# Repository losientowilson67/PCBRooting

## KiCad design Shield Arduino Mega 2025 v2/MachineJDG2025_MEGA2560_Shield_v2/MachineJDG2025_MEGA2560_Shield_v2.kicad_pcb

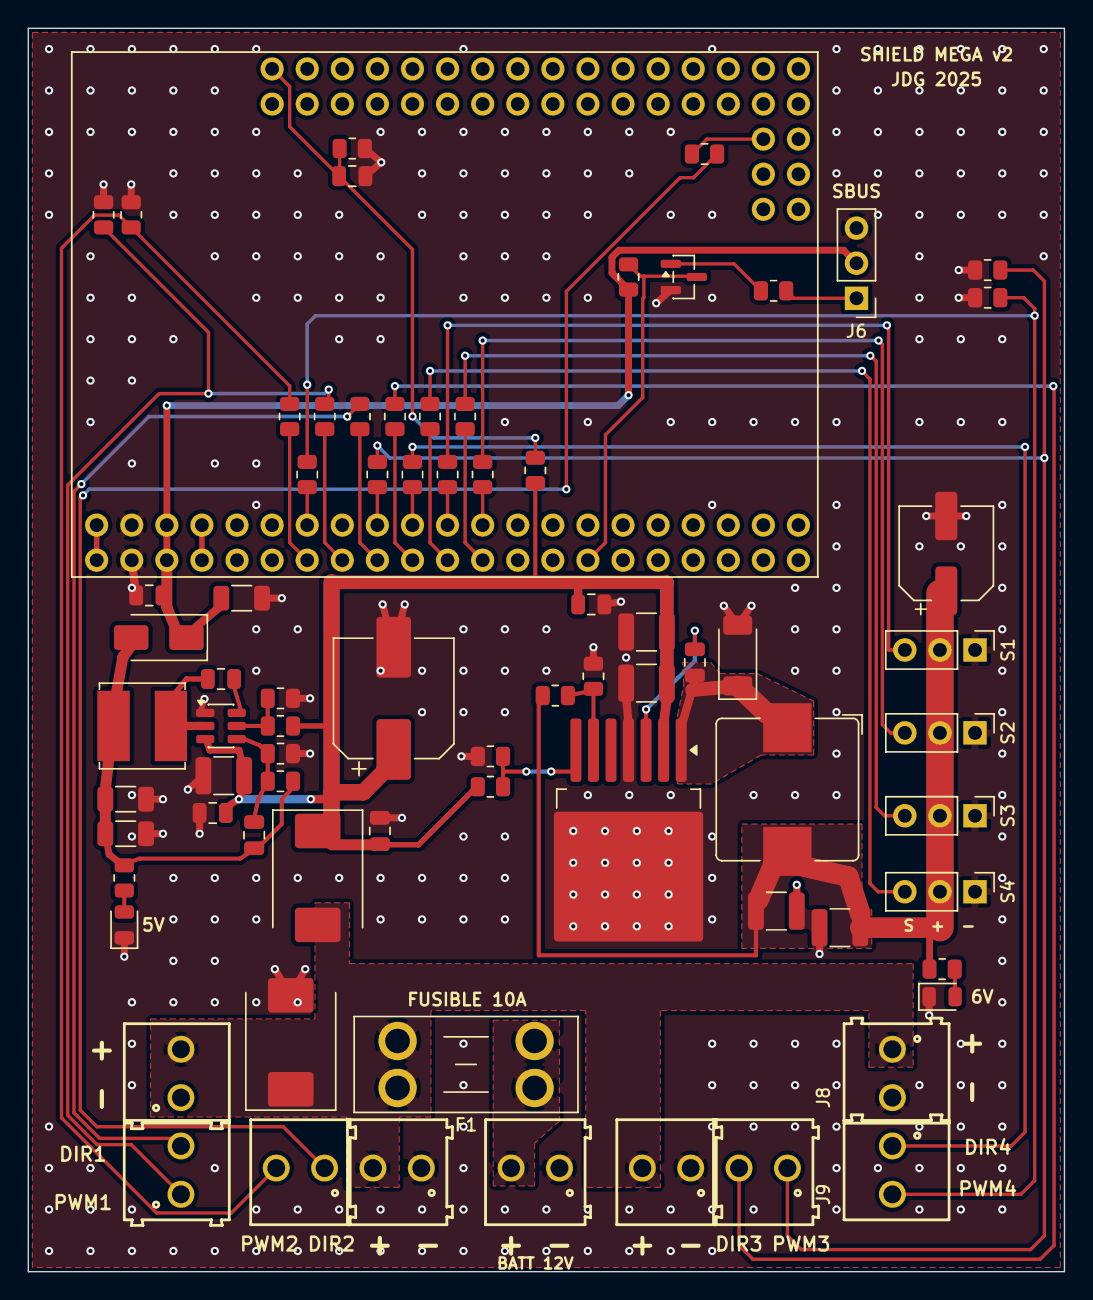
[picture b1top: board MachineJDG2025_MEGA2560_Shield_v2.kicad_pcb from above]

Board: 2 copper layers, 75.0 x 90.0 mm, 75 parts (0 on the bottom side), 45 nets.

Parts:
C1: 220uF 35V; CP_Elec_8x10.5
C2, C5, C11, C12, C17, C18: 100nF 50V; C_0805_2012Metric
C3, C4, C10: 10uF 50V; C_1210_3225Metric
C6: 10nF 50V; C_0805_2012Metric
C7, C8: 22uF 25V; C_1210_3225Metric
C9: 220uF 16V; CP_Elec_6.3x7.7
C13: 75pF; C_0805_2012Metric
C14, C15: 22uF 16V; C_1206_3216Metric
C16: 10uF 16V; C_1206_3216Metric
D1: SMCJ15A; D_SMC
D2: SS54; D_SMC
D3: PMEG4050EP; D_SOD-128
D4: SS34; D_SMA
F1: Fusible mini-lame 10A; Fuseholder_Blade_Mini_Keystone_3568
J1: BATT 12V; 691214110002
J2: MOT1 PWR; 691214110002
J3: MOT1 PWM/DIR; 691214110002
J4: MOT3 PWR; 691214110002
J5: MOT3 PWM/DIR; 691214110002
J6: SBUS; PinHeader_1x03_P2.54mm_Vertical
J8: MOT4 PWR; 691214110002
J9: MOT4 DIR/PWM; 691214110002
J10: MOT2 PWR; 691214110002
J11: MOT2 DIR/PWM; 691214110002
L1: 4.7uH; L_Bourns_SRP1038C_10.0x10.0mm
L2: 15uH; L_Bourns_SRN6045TA
LED1: LED verte 6V; LED_0805_2012Metric
LED2: LED verte 5V; LED_0805_2012Metric
Q1: MMBT3904; SOT-23
R1, R7, R12: 1k; R_0805_2012Metric
R2: 10k; R_0805_2012Metric
R3, R8: 100k; R_0805_2012Metric
R4, R9: 33k; R_0805_2012Metric
R5: 182R 1%; R_0805_2012Metric
R6: 1k 1%; R_0805_2012Metric
R10: 100k 1%; R_0805_2012Metric
R11: 12.7k 1%; R_0805_2012Metric
R13: 30k 1%; R_0805_2012Metric
R14: 10k 1%; R_0805_2012Metric
R20, R21, R22, R23, R24, R25, R26, R27, R40, R41, R42, R43: 100R; R_0805_2012Metric
R30, R31, R32, R33: 4.7k; R_0805_2012Metric
S1: SERVO1; PinHeader_1x03_P2.54mm_Vertical
S2: SERVO2; PinHeader_1x03_P2.54mm_Vertical
S3: SERVO3; PinHeader_1x03_P2.54mm_Vertical
S4: SERVO4; PinHeader_1x03_P2.54mm_Vertical
U1: Mega 2560 PRO Embed; MODULE_MEGA_PRO_EMBED_CH340G_ATMEGA2560
U2: LM22678TJ-5.0; TO-263-7_TabPin8
U3: TPS54202H; SOT-23-6

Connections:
/5V_BUCK: C13.1, C14.1, C15.1, D4.2, L2.2, R10.1, R12.1
/+5V: C16.1, C17.1, D4.1, J6.2, R2.1, U1.5V_1, U1.5V_2
/+6V: C7.1, C8.1, C9.1, L1.2, R5.1, R7.1, S1.2, S2.2, S3.2, S4.2
/BOOT5: C12.1, U3.6
/BOOT6: C6.1, U2.3
/D2: R26.1, U1.D2
/D3: R22.1, U1.D3
/D5: R20.1, U1.D5
/D6: R24.1, U1.D6
/D7: R21.1, U1.D7
/D8: R27.1, U1.D8
/D9: R25.1, U1.D9
/D10: R40.1, U1.D10
/D11: R43.1, U1.D11
/D12: R41.1, U1.D12
/D13: R42.1, U1.D13
/D19: Q1.3, R2.2, U1.D19
/D49: R23.1, U1.D49
/EN5: R8.2, R9.1, U3.5
/EN6: R3.2, R4.1, U2.7
/FB5: C13.2, R10.2, R11.1, U3.4
/FB6: R5.2, R6.1, U2.6
/GND: C1.2, C2.2, C3.2, C4.2, C5.2, C7.2, C8.2, C9.2, C10.2, C11.2, C14.2, C15.2, C16.2, C17.2, C18.2, D1.2, D3.2, J1.1, J2.1, J4.1, J6.3, J8.2, J10.1, LED1.1, LED2.1, Q1.2, R4.2, R6.2, R9.2, R11.2, R14.2, R30.2, R31.2, R32.2, R33.2, S1.1, S2.1, S3.1, S4.1, U1.GND_1, U1.GND_2, U2.4, U2.8, U3.1
/LED5: LED2.2, R12.2
/LED6: LED1.2, R7.2
/M1_DIR: J3.2, R21.2
/M1_PWM: J3.1, R20.2, R30.1
/M2_DIR: J11.1, R23.2
/M2_PWM: J11.2, R22.2, R31.1
/M3_DIR: J5.2, R25.2
/M3_PWM: J5.1, R24.2, R32.1
/M4_DIR: J9.1, R27.2
/M4_PWM: J9.2, R26.2, R33.1
/SBUS_B: Q1.1, R1.2
/SBUS_IN: J6.1, R1.1
/SERVO1_SIG: R40.2, S1.3
/SERVO2_SIG: R41.2, S2.3
/SERVO3_SIG: R42.2, S3.3
/SERVO4_SIG: R43.2, S4.3
/SW5: C12.2, L2.1, U3.2
/SW6: C6.2, D3.1, L1.1, U2.1
/V12: C1.1, C2.1, C3.1, C4.1, C5.1, C10.1, C11.1, D2.1, R3.1, R8.1, R13.1, U2.2, U3.3
/VBAT: D1.1, D2.2, F1.2, J2.2, J4.2, J8.1, J10.2
/VBAT_IN: F1.1, J1.2
/VBAT_SENSE: C18.1, R13.2, R14.1, U1.A0

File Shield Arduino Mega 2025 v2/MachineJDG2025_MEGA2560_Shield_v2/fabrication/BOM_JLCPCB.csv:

Comment,Designator,Footprint,LCSC Part #
220uF 35V,C1,CP_Elec_8x10.5,
100nF 50V,"C2,C5,C11,C12,C17,C18",C_0805_2012Metric,C49678
10uF 50V,"C3,C4,C10",C_1210_3225Metric,
10nF 50V,C6,C_0805_2012Metric,
22uF 25V,"C7,C8",C_1210_3225Metric,
220uF 16V,C9,CP_Elec_6.3x7.7,
75pF,C13,C_0805_2012Metric,
22uF 16V,"C14,C15",C_1206_3216Metric,
10uF 16V,C16,C_1206_3216Metric,
SMCJ15A,D1,D_SMC,
SS54,D2,D_SMC,
PMEG4050EP,D3,D_SOD-128,
SS34,D4,D_SMA,C8678
4.7uH,L1,L_Bourns_SRP1038C_10.0x10.0mm,
15uH,L2,L_Bourns_SRN6045TA,
LED verte 6V,LED1,LED_0805_2012Metric,
LED verte 5V,LED2,LED_0805_2012Metric,
MMBT3904,Q1,SOT-23,C20526
1k,"R1,R7,R12",R_0805_2012Metric,C17513
10k,R2,R_0805_2012Metric,C17414
100k,"R3,R8",R_0805_2012Metric,C17407
33k,"R4,R9",R_0805_2012Metric,
182R 1%,R5,R_0805_2012Metric,
1k 1%,R6,R_0805_2012Metric,C17513
100k 1%,R10,R_0805_2012Metric,C17407
12.7k 1%,R11,R_0805_2012Metric,
30k 1%,R13,R_0805_2012Metric,
10k 1%,R14,R_0805_2012Metric,C17414
100R,"R20,R21,R22,R23,R24,R25,R26,R27,R40,R41,R42,R43",R_0805_2012Metric,C17408
LM22678TJ-5.0,U2,TO-263-7_TabPin8,C527397
TPS54202H,U3,SOT-23-6,C527684

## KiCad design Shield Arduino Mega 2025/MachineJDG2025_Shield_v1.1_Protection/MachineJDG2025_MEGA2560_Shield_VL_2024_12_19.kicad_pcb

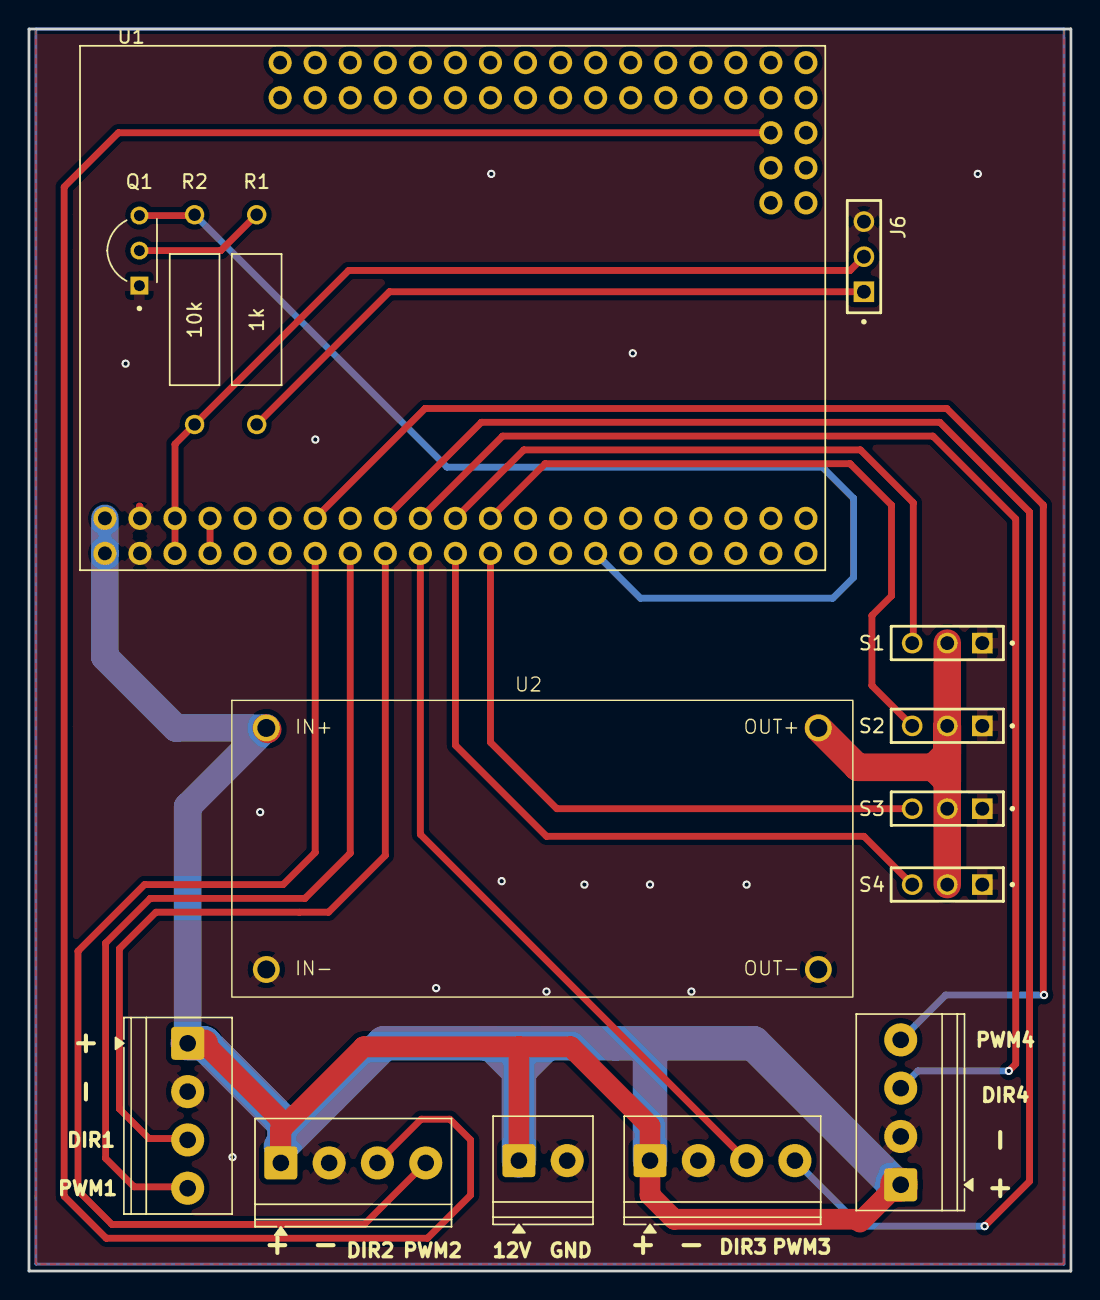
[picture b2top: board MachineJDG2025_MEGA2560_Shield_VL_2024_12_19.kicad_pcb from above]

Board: 2 copper layers, 75.5 x 90.0 mm, 15 parts (0 on the bottom side), 20 nets.

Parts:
J1: 691214110002; TerminalBlock_Phoenix_PT-1,5-2-3.5-H_1x02_P3.50mm_Horizontal
J2, J3, J4, J5: Screw_Terminal_01x04; TerminalBlock_Phoenix_PT-1,5-4-3.5-H_1x04_P3.50mm_Horizontal
J6: SSW-103-01-F-D; SAMTEC_SSW-103-01-F-D_3X1
Q1: 2N2222A; TO92254P470H750-3
R1: 1k; RESAD1520W70L1030D380
R2: 10k; RESAD1520W70L1030D380
S1, S2, S3, S4: SSW-103-01-F-D; SAMTEC_SSW-103-01-F-D_3X1
U1: MEGA_PRO_EMBED_CH340G___ATMEGA2560; MODULE_MEGA_PRO_EMBED_CH340G___ATMEGA2560
U2: LM2596; LM2956

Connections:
3V3: U1.3V3_1 (3V3), U1.3V3_2 (3V3)
5V: J6.02, R2.1, U1.5V_1 (5V), U1.5V_2 (5V)
6V: S1.02, S2.02, S3.02, S4.02, U2.3 (Vout+)
12V: J1.1, J2.1, J3.1, J4.1, J5.1, U1.VIN_1 (VIN), U1.VIN_2 (VIN), U2.1 (Vin+)
D2: J5.4, U1.D2
D3: J4.4, U1.D3
D5: J2.4, U1.D5
D6: J3.4, U1.D6
D7: J2.3, U1.D7
D8: J5.3, U1.D8
D9: J3.3, U1.D9
D10: S1.03, U1.D10
D11: S4.03, U1.D11
D12: S2.03, U1.D12
D13: S3.03, U1.D13
D19: Q1.3, R2.2, U1.D19
D49: J4.3, U1.D49
GND: J1.2, J2.2, J3.2, J4.2, J5.2, J6.03, Q1.1, S1.01, S2.01, S3.01, S4.01, U1.GND_1 (GND), U1.GND_2 (GND), U2.2 (Vin-), U2.4 (Vout-)
unnamed: Q1.2, R1.2
S_BUS: J6.01, R1.1

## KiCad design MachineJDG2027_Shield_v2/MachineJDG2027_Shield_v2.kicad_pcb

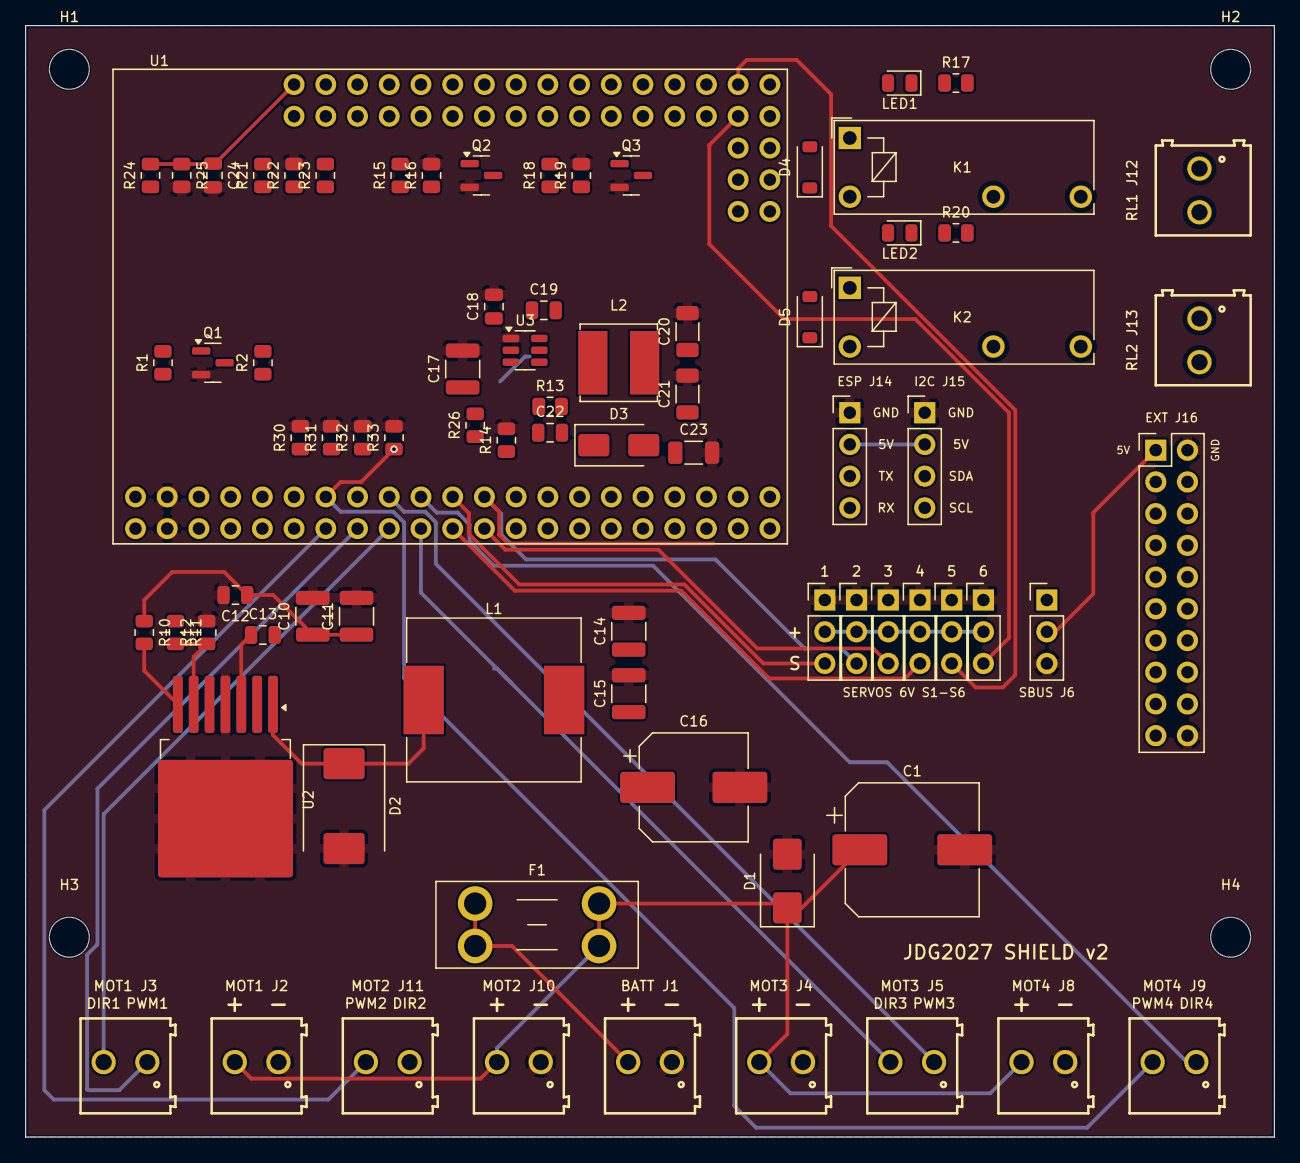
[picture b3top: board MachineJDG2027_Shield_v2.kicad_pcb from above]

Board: 2 copper layers, 100.0 x 89.0 mm, 82 parts (0 on the bottom side), 66 nets.

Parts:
C1: 470uF 25V; CP_Elec_10x10.5
C10, C11, C17: 10uF 50V; C_1210_3225Metric
C12: 1uF 50V; C_0805_2012Metric
C13: 10nF 50V; C_0805_2012Metric
C14, C15: 22uF 25V; C_1210_3225Metric
C16: 220uF 16V; CP_Elec_8x10.5
C18, C19, C24: 100nF; C_0805_2012Metric
C20, C21: 22uF 16V; C_1206_3216Metric
C22: 75pF; C_0805_2012Metric
C23: 10uF 16V; C_1206_3216Metric
D1: SMBJ15A; D_SMB
D2: SS54; D_SMC
D3: SS34; D_SMA
D4, D5: 1N4148W; D_SOD-123
F1: 10A mini-lame; Fuseholder_Blade_Mini_Keystone_3568
H1, H2, H3, H4: M3; MountingHole_3.2mm_M3
J1: BATT_IN; 691214110002
J2: MOT_PWR1; 691214110002
J3: MOT1 PWM/DIR; 691214110002
J4: MOT_PWR3; 691214110002
J5: MOT3 PWM/DIR; 691214110002
J6: SBUS; PinHeader_1x03_P2.54mm_Vertical
J8: MOT_PWR4; 691214110002
J9: MOT4 DIR/PWM; 691214110002
J10: MOT_PWR2; 691214110002
J11: MOT2 DIR/PWM; 691214110002
J12: RELAIS1; 691214110002
J13: RELAIS2; 691214110002
J14: UART2_ESP; PinHeader_1x04_P2.54mm_Vertical
J15: I2C; PinHeader_1x04_P2.54mm_Vertical
J16: EXT_IO; PinHeader_2x10_P2.54mm_Vertical
K1, K2: G5NB-1A-E DC5V; Relay_SPST_Omron_G5NB
L1: 4.7uH; L_Sunlord_MWSA1265S
L2: 15uH; L_Bourns_SRN6045TA
LED1, LED2: LED verte; LED_0805_2012Metric
Q1: MMBT3904; SOT-23
Q2, Q3: 2N7002; SOT-23
R1, R17, R20, R21, R23: 1k; R_0805_2012Metric
R2, R16, R19: 10k; R_0805_2012Metric
R10: 470k; R_0805_2012Metric
R11: 182R 1%; R_0805_2012Metric
R12: 1k 1%; R_0805_2012Metric
R13: 100k 1%; R_0805_2012Metric
R14: 12.7k 1%; R_0805_2012Metric
R15, R18: 100R; R_0805_2012Metric
R22: 2k; R_0805_2012Metric
R24: 30k 1%; R_0805_2012Metric
R25: 10k 1%; R_0805_2012Metric
R26: 510k; R_0805_2012Metric
R30, R31, R32, R33: 4.7k DNP; R_0805_2012Metric
S1: SERVO1; PinHeader_1x03_P2.54mm_Vertical
S2: SERVO2; PinHeader_1x03_P2.54mm_Vertical
S3: SERVO3; PinHeader_1x03_P2.54mm_Vertical
S4: SERVO4; PinHeader_1x03_P2.54mm_Vertical
S5: SERVO5; PinHeader_1x03_P2.54mm_Vertical
S6: SERVO6; PinHeader_1x03_P2.54mm_Vertical
U1: Mega2560 PRO Embed; MODULE_MEGA_PRO_EMBED_CH340G_ATMEGA2560
U2: LM22678TJ-5.0; TO-263-7_TabPin8
U3: TPS54202H; SOT-23-6

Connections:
+5V: C23.1, D3.1, D4.1, D5.1, J6.2, J14.2, J15.2, J16.1, J16.19, K1.A1, K2.A1, R2.1, R17.1, R20.1, U1.5V_1, U1.5V_2
+5V_BUCK: C20.1, C21.1, C22.1, D3.2, L2.2, R13.1
+6V: C14.1, C15.1, C16.1, L1.2, R11.1, S1.2, S2.2, S3.2, S4.2, S5.2, S6.2
A0: C24.1, R24.2, R25.1, U1.A0
A1: J16.3, U1.A1
A2: J16.4, U1.A2
A3: J16.5, U1.A3
A4: J16.6, U1.A4
A5: J16.7, U1.A5
A6: J16.8, U1.A6
A7: J16.9, U1.A7
BOOT5: C19.1, U3.6
BOOT6: C13.1, U2.3
D2: J9.2, R33.1, U1.D2
D3: J11.2, R31.1, U1.D3
D5: J3.1, R30.1, U1.D5
D6: J5.1, R32.1, U1.D6
D7: J3.2, U1.D7
D8: J9.1, U1.D8
D9: J5.2, U1.D9
D10: S1.3, U1.D10
D11: S4.3, U1.D11
D12: S2.3, U1.D12
D13: S3.3, U1.D13
D16: R21.1, U1.D16
D17: R23.2, U1.D17
D19: Q1.3, R2.2, U1.D19
D20: J15.3, U1.D20
D21: J15.4, U1.D21
D22: R15.1, U1.D22
D23: R18.1, U1.D23
D24: J16.10, U1.D24
D25: J16.11, U1.D25
D26: J16.12, U1.D26
D27: J16.13, U1.D27
D28: J16.14, U1.D28
D29: J16.15, U1.D29
D30: J16.16, U1.D30
D31: J16.17, U1.D31
D32: J16.18, U1.D32
D44: S5.3, U1.D44
D45: S6.3, U1.D45
D49: J11.1, U1.D49
EN5: R26.2, U3.5
EN6: R10.2, U2.7
ESP_RX: J14.3, R21.2, R22.1
ESP_TX: J14.4, R23.1
FB5: C22.2, R13.2, R14.1, U3.4
FB6: R11.2, R12.1, U2.6
GND: C1.2, C10.2, C11.2, C12.2, C14.2, C15.2, C16.2, C17.2, C18.2, C20.2, C21.2, C23.2, C24.2, D1.2, D2.2, J1.1, J2.1, J4.1, J6.3, J8.1, J10.1, J14.1, J15.1, J16.2, J16.20, Q1.2, Q2.2, Q3.2, R12.2, R14.2, R16.2, R19.2, R22.2, R25.2, R30.2, R31.2, R32.2, R33.2, S1.1, S2.1, S3.1, S4.1, S5.1, S6.1, U1.GND_1, U1.GND_2, U2.4, U2.8, U3.1
K1_DRV: D4.2, K1.A2, LED1.1, Q2.3
K1_G: Q2.1, R15.2, R16.1
K1_LED: LED1.2, R17.2
K2_DRV: D5.2, K2.A2, LED2.1, Q3.3
K2_G: Q3.1, R18.2, R19.1
K2_LED: LED2.2, R20.2
RL1_A: J12.1, K1.13
RL1_B: J12.2, K1.14
RL2_A: J13.1, K2.13
RL2_B: J13.2, K2.14
SBUS_B: Q1.1, R1.2
SW5: C19.2, L2.1, U3.2
SW6: C13.2, D2.1, L1.1, U2.1
S_BUS: J6.1, R1.1
VBAT: C1.1, C10.1, C11.1, C12.1, C17.1, C18.1, D1.1, F1.2, J2.2, J4.2, J8.2, J10.2, R10.1, R24.1, R26.1, U2.2, U3.3
VBAT_IN: F1.1, J1.2

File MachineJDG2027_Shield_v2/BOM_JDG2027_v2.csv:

Comment,Designator,Footprint,LCSC Part #,MPN,Qty,Montage
470uF 25V,C1,CP_Elec_10x10.5,,470uF 25V 10x10.5,1,CMS - assemblage JLC
10uF 50V,"C10,C11,C17",C_1210_3225Metric,,,3,CMS - assemblage JLC
1uF 50V,C12,C_0805_2012Metric,,,1,CMS - assemblage JLC
10nF 50V,C13,C_0805_2012Metric,,,1,CMS - assemblage JLC
22uF 25V,"C14,C15",C_1210_3225Metric,,,2,CMS - assemblage JLC
220uF 16V,C16,CP_Elec_8x10.5,,220uF 16V 8x10.5,1,CMS - assemblage JLC
100nF,"C18,C19,C24",C_0805_2012Metric,,,3,CMS - assemblage JLC
22uF 16V,"C20,C21",C_1206_3216Metric,,,2,CMS - assemblage JLC
75pF,C22,C_0805_2012Metric,,,1,CMS - assemblage JLC
10uF 16V,C23,C_1206_3216Metric,,,1,CMS - assemblage JLC
SMBJ15A,D1,D_SMB,,SMBJ15A,1,CMS - assemblage JLC
SS54,D2,D_SMC,,SS54 (5A 40V),1,CMS - assemblage JLC
SS34,D3,D_SMA,,SS34,1,CMS - assemblage JLC
1N4148W,"D4,D5",D_SOD-123,,,2,CMS - assemblage JLC
4.7uH,L1,L_Sunlord_MWSA1265S,,MWSA1265S-4R7MT,1,CMS - assemblage JLC
15uH,L2,L_Bourns_SRN6045TA,,SRN6045TA-150M,1,CMS - assemblage JLC
LED verte,"LED1,LED2",LED_0805_2012Metric,,,2,CMS - assemblage JLC
MMBT3904,Q1,SOT-23,,,1,CMS - assemblage JLC
2N7002,"Q2,Q3",SOT-23,,,2,CMS - assemblage JLC
1k,"R1,R17,R20,R21,R23",R_0805_2012Metric,,,5,CMS - assemblage JLC
10k,"R2,R16,R19",R_0805_2012Metric,,,3,CMS - assemblage JLC
470k,R10,R_0805_2012Metric,,,1,CMS - assemblage JLC
182R 1%,R11,R_0805_2012Metric,,,1,CMS - assemblage JLC
1k 1%,R12,R_0805_2012Metric,,,1,CMS - assemblage JLC
100k 1%,R13,R_0805_2012Metric,,,1,CMS - assemblage JLC
12.7k 1%,R14,R_0805_2012Metric,,,1,CMS - assemblage JLC
100R,"R15,R18",R_0805_2012Metric,,,2,CMS - assemblage JLC
2k,R22,R_0805_2012Metric,,,1,CMS - assemblage JLC
30k 1%,R24,R_0805_2012Metric,,,1,CMS - assemblage JLC
10k 1%,R25,R_0805_2012Metric,,,1,CMS - assemblage JLC
510k,R26,R_0805_2012Metric,,,1,CMS - assemblage JLC
LM22678TJ-5.0,U2,TO-263-7_TabPin8,C527397,LM22678TJ-5.0/NOPB,1,CMS - assemblage JLC
TPS54202H,U3,SOT-23-6,C527684,TPS54202HDDCR,1,CMS - assemblage JLC
10A mini-lame,F1,Fuseholder_Blade_Mini_Keystone_3568,,Keystone 3568 + fusible mini-lame 10A,1,THT - soudure main
Bornier Wurth 691214110002 (2P 3.5mm),"J1,J2,J3,J4,J5,J8,J9,J10,J11,J12,J13",691214110002,,,11,THT - soudure main
Header male 1x03 2.54mm,"J6,S1,S2,S3,S4,S5,S6",PinHeader_1x03_P2.54mm_Vertical,,,7,THT - soudure main
Header male 1x04 2.54mm,"J14,J15",PinHeader_1x04_P2.54mm_Vertical,,,2,THT - soudure main
Header male 2x10 2.54mm,J16,PinHeader_2x10_P2.54mm_Vertical,,,1,THT - soudure main
G5NB-1A-E DC5V,"K1,K2",Relay_SPST_Omron_G5NB,C48746,G5NB-1A-E-DC5V,2,THT - soudure main
Mega 2560 PRO Embed + embases femelles 2x21, 2x16 et 2x3 (2.54mm),U1,MODULE_MEGA_PRO_EMBED_CH340G_ATMEGA2560,,Mega 2560 PRO Embed CH340G,1,THT - soudure main
4.7k DNP,"R30,R31,R32,R33",R_0805_2012Metric,,,4,NE PAS POSER (DNP)
